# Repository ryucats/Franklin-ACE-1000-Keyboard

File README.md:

# Franklin-ACE-1000-Keyboard
Replacement Franklin ACE 1000 keyboard for use with osiweb's Unified Retro Keyboard

## Images

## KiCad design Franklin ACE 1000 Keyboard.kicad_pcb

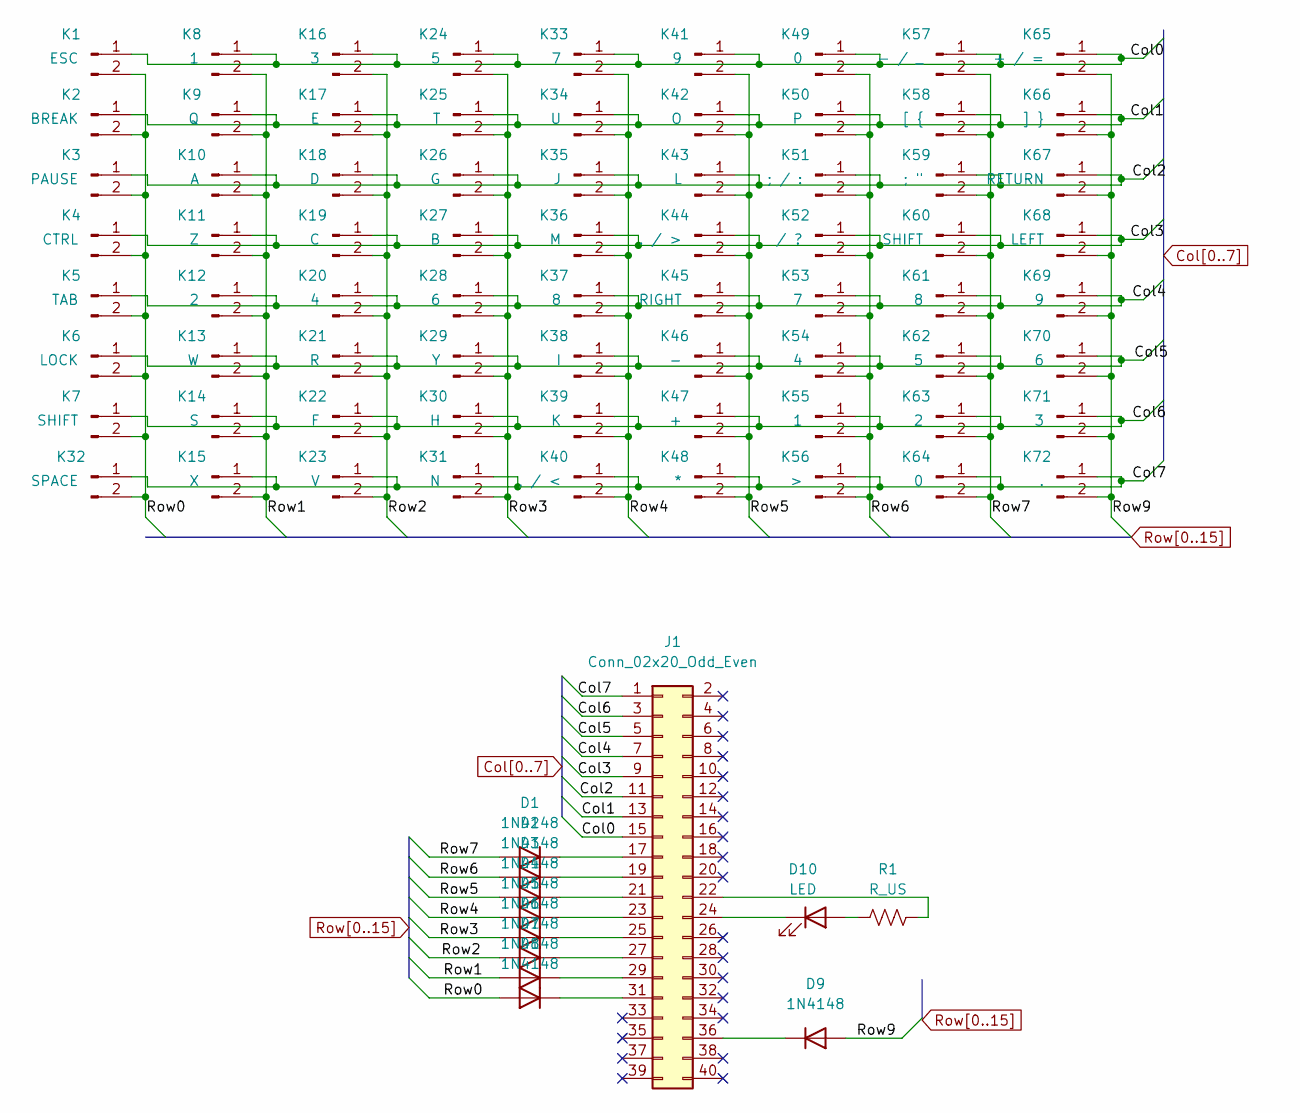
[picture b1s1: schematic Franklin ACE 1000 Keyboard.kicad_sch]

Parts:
D1, D2, D3, D4, D5, D6, D7, D8, D9: 1N4148; D_DO-35_SOD27_P7.62mm_Horizontal
D10: LED; LED_D3.0mm
J1: Conn_02x20_Odd_Even; PinHeader_2x20_P2.54mm_Vertical
K1: ESC; SW_Cherry_MX_1.00u_PCB
K2: BREAK; SW_Cherry_MX_1.00u_PCB
K3: PAUSE; SW_Cherry_MX_1.00u_PCB
K4: CTRL; SW_Cherry_MX_1.00u_PCB
K5: TAB; SW_Cherry_MX_1.00u_PCB
K6: LOCK; SW_Cherry_MX_1.00u_PCB
K7, K60: SHIFT; SW_Cherry_MX_1.00u_PCB
K8, K55: 1; SW_Cherry_MX_1.00u_PCB
K9: Q; SW_Cherry_MX_1.00u_PCB
K10: A; SW_Cherry_MX_1.00u_PCB
K11: Z; SW_Cherry_MX_1.00u_PCB
K12, K63: 2; SW_Cherry_MX_1.00u_PCB
K13: W; SW_Cherry_MX_1.00u_PCB
K14: S; SW_Cherry_MX_1.00u_PCB
K15: X; SW_Cherry_MX_1.00u_PCB
K16, K71: 3; SW_Cherry_MX_1.00u_PCB
K17: E; SW_Cherry_MX_1.00u_PCB
K18: D; SW_Cherry_MX_1.00u_PCB
K19: C; SW_Cherry_MX_1.00u_PCB
K20, K54: 4; SW_Cherry_MX_1.00u_PCB
K21: R; SW_Cherry_MX_1.00u_PCB
K22: F; SW_Cherry_MX_1.00u_PCB
K23: V; SW_Cherry_MX_1.00u_PCB
K24, K62: 5; SW_Cherry_MX_1.00u_PCB
K25: T; SW_Cherry_MX_1.00u_PCB
K26: G; SW_Cherry_MX_1.00u_PCB
K27: B; SW_Cherry_MX_1.00u_PCB
K28, K70: 6; SW_Cherry_MX_1.00u_PCB
K29: Y; SW_Cherry_MX_1.00u_PCB
K30: H; SW_Cherry_MX_1.00u_PCB
K31: N; SW_Cherry_MX_1.00u_PCB
K32: SPACE; SW_Cherry_MX_1.00u_PCB
K33, K53: 7; SW_Cherry_MX_1.00u_PCB
K34: U; SW_Cherry_MX_1.00u_PCB
K35: J; SW_Cherry_MX_1.00u_PCB
K36: M; SW_Cherry_MX_1.00u_PCB
K37, K61: 8; SW_Cherry_MX_1.00u_PCB
K38: I; SW_Cherry_MX_1.00u_PCB
K39: K; SW_Cherry_MX_1.00u_PCB
K40: , / <; SW_Cherry_MX_1.00u_PCB
K41, K69: 9; SW_Cherry_MX_1.00u_PCB
K42: O; SW_Cherry_MX_1.00u_PCB
K43: L; SW_Cherry_MX_1.00u_PCB
K44: . / >; SW_Cherry_MX_1.00u_PCB
K45: RIGHT; SW_Cherry_MX_1.00u_PCB
K46: -; SW_Cherry_MX_1.00u_PCB
K47: +; SW_Cherry_MX_1.00u_PCB
K48: *; SW_Cherry_MX_1.00u_PCB
K49, K64: 0; SW_Cherry_MX_1.00u_PCB
K50: P; SW_Cherry_MX_1.00u_PCB
K51: ; / :; SW_Cherry_MX_1.00u_PCB
K52: / ?; SW_Cherry_MX_1.00u_PCB
K56: >; SW_Cherry_MX_1.00u_PCB
K57: - / _; SW_Cherry_MX_1.00u_PCB
K58: [ {; SW_Cherry_MX_1.00u_PCB
K59: ; "; SW_Cherry_MX_1.00u_PCB
K65: + / =; SW_Cherry_MX_1.00u_PCB
K66: ] }; SW_Cherry_MX_1.00u_PCB
K67: RETURN; SW_Cherry_MX_1.00u_PCB
K68: LEFT; SW_Cherry_MX_1.00u_PCB
K72: .; SW_Cherry_MX_1.00u_PCB
R1: R_US; R_Axial_DIN0207_L6.3mm_D2.5mm_P7.62mm_Horizontal

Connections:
Col0: J1.15, K1.1, K8.1, K16.1, K24.1, K33.1, K41.1, K49.1, K57.1, K65.1
Col1: J1.13, K2.1, K9.1, K17.1, K25.1, K34.1, K42.1, K50.1, K58.1, K66.1
Col2: J1.11, K3.1, K10.1, K18.1, K26.1, K35.1, K43.1, K51.1, K59.1, K67.1
Col3: J1.9, K4.1, K11.1, K19.1, K27.1, K36.1, K44.1, K52.1, K60.1, K68.1
Col4: J1.7, K5.1, K12.1, K20.1, K28.1, K37.1, K45.1, K53.1, K61.1, K69.1
Col5: J1.5, K6.1, K13.1, K21.1, K29.1, K38.1, K46.1, K54.1, K62.1, K70.1
Col6: J1.3, K7.1, K14.1, K22.1, K30.1, K39.1, K47.1, K55.1, K63.1, K71.1
Col7: J1.1, K15.1, K23.1, K31.1, K32.1, K40.1, K48.1, K56.1, K64.1, K72.1
unnamed: D1.1 (K), J1.17
unnamed: D2.1 (K), J1.19
unnamed: D3.1 (K), J1.21
unnamed: D4.1 (K), J1.23
unnamed: D5.1 (K), J1.25
unnamed: D6.1 (K), J1.27
unnamed: D7.1 (K), J1.29
unnamed: D8.1 (K), J1.31
unnamed: D9.1 (K), J1.36
unnamed: D10.2 (A), R1.1
unnamed: D10.1 (K), J1.24
unnamed: J1.22, R1.2
Row0: D8.2 (A), K1.2, K2.2, K3.2, K4.2, K5.2, K6.2, K7.2, K32.2
Row1: D7.2 (A), K8.2, K9.2, K10.2, K11.2, K12.2, K13.2, K14.2, K15.2
Row2: D6.2 (A), K16.2, K17.2, K18.2, K19.2, K20.2, K21.2, K22.2, K23.2
Row3: D5.2 (A), K24.2, K25.2, K26.2, K27.2, K28.2, K29.2, K30.2, K31.2
Row4: D4.2 (A), K33.2, K34.2, K35.2, K36.2, K37.2, K38.2, K39.2, K40.2
Row5: D3.2 (A), K41.2, K42.2, K43.2, K44.2, K45.2, K46.2, K47.2, K48.2
Row6: D2.2 (A), K49.2, K50.2, K51.2, K52.2, K53.2, K54.2, K55.2, K56.2
Row7: D1.2 (A), K57.2, K58.2, K59.2, K60.2, K61.2, K62.2, K63.2, K64.2
Row9: D9.2 (A), K65.2, K66.2, K67.2, K68.2, K69.2, K70.2, K71.2, K72.2

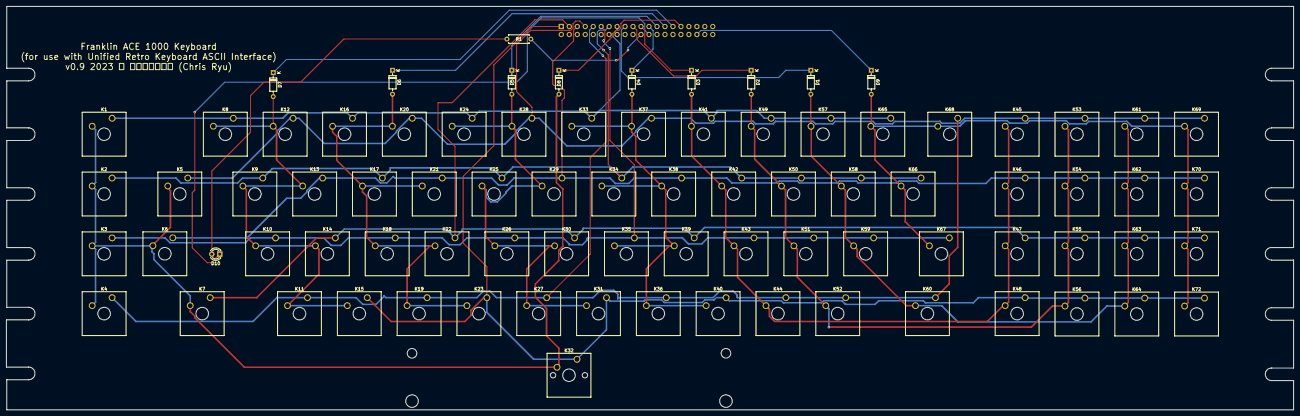
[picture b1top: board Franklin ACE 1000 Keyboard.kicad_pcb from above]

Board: 2 copper layers, 410.0 x 128.5 mm, 84 parts (1 on the bottom side), 29 nets.

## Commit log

2023-03-17 Initial commit.
2023-03-18 Oops, commit actual production board.
2023-03-18 Add images.
2023-03-18 Re-order.
